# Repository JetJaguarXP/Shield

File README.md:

# USB / DC / Solar Charger, Fuel gauge, Buck-Boost Shield
# Released under the Creative Commons Attribution-ShareAlike 4.0 International License.

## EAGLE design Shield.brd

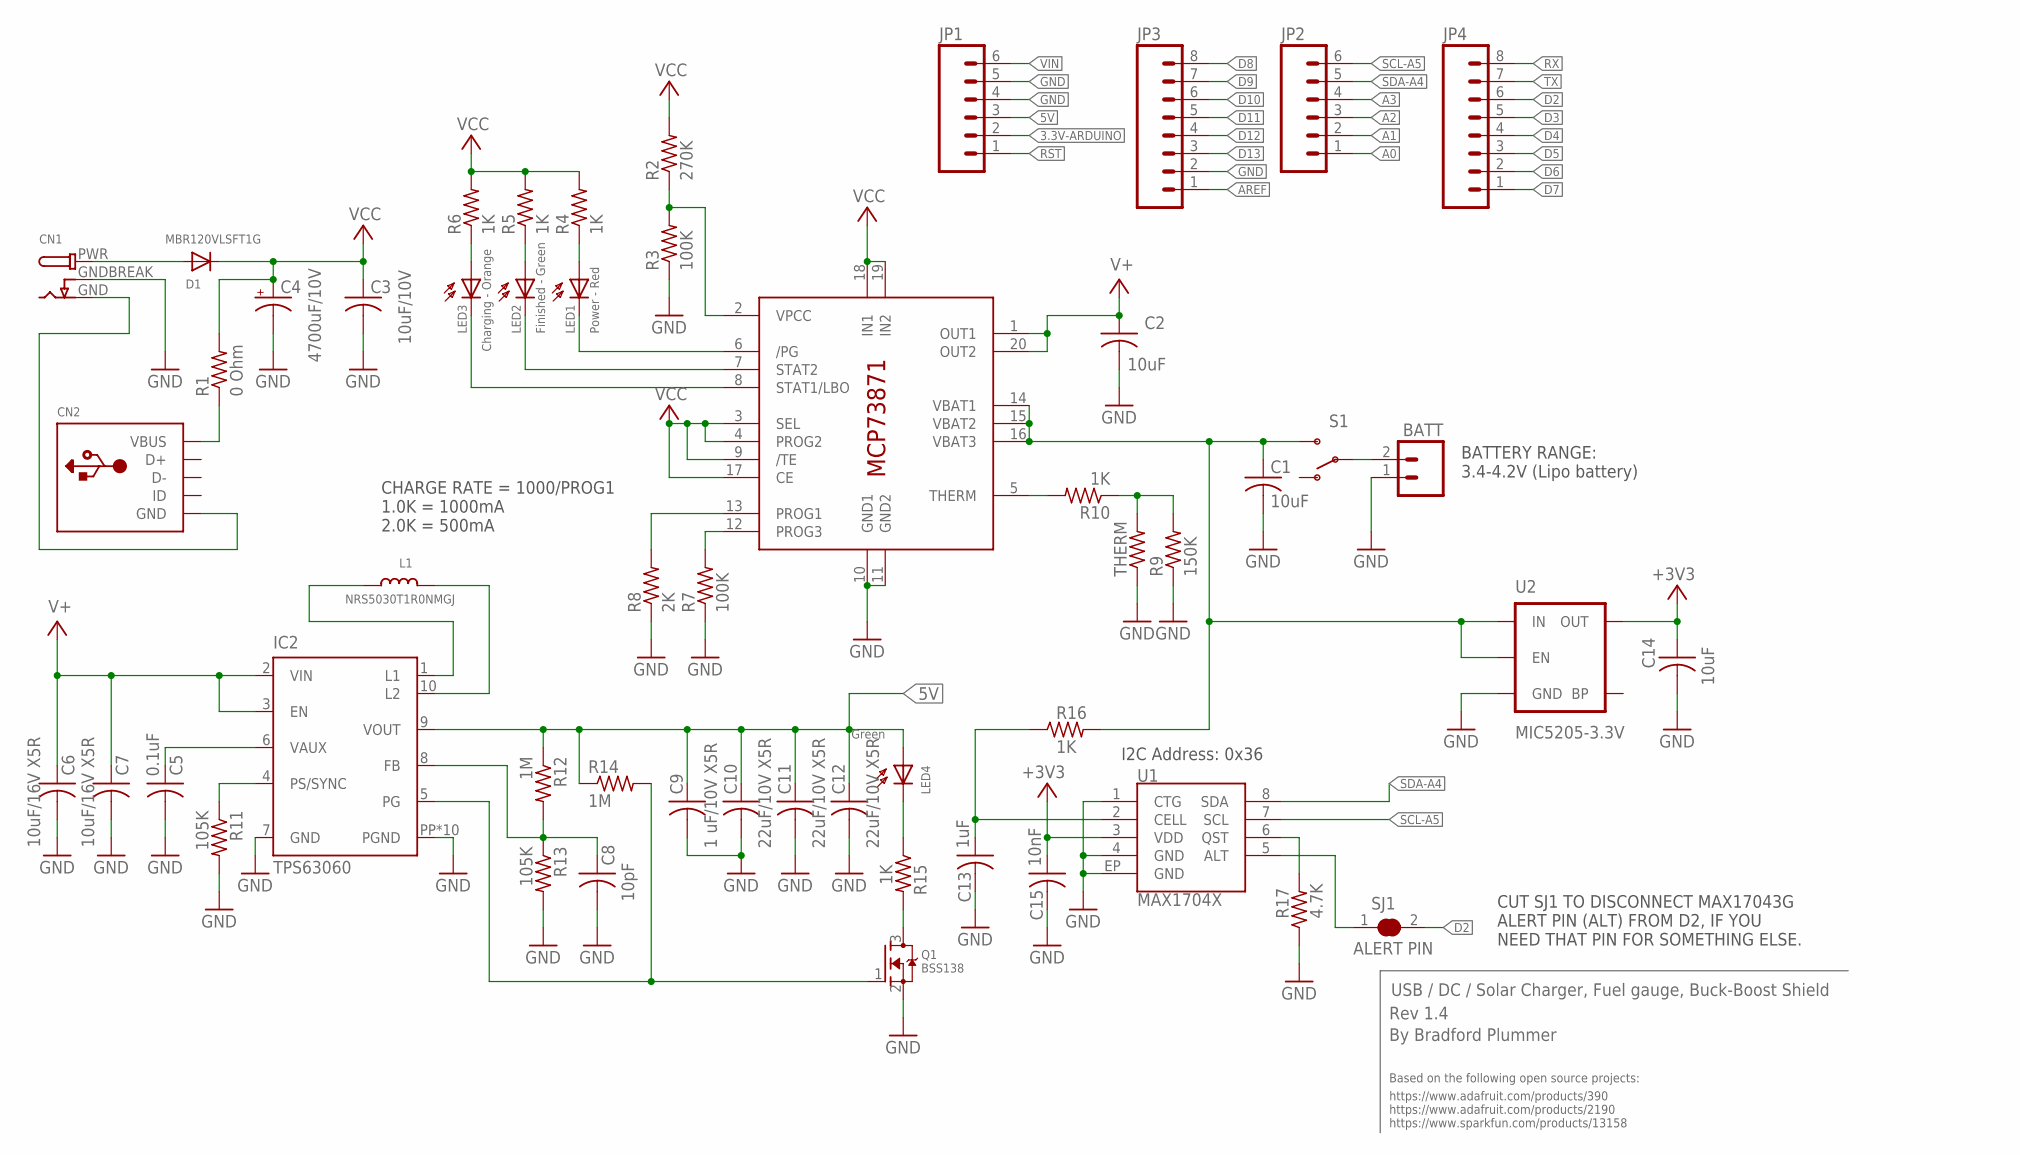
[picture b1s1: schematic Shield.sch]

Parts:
BATT: M02JST-PTH-VERT; JST-2-PTH-VERT
C1, C2, C14: 10uF; C0805K
C3: 10uF/10V; C0805K
C4: 4700uF/10V; E5-13
C5: 0.1uF; C0805K
C6, C7: 10uF/16V X5R; C0805K
C8: 10pF; C0805K
C9: 1 uF/10V X5R; C0805K
C10, C11, C12: 22uF/10V X5R; C0805K
C13: 1uF; C0805K
C15: 10nF; C0805K
CN1: DCBARREL1.3MM; DCJACK_1.3MM_PTH
CN2: USBMINIB; USB-MINIB
D1: MBR120VLSFT1G; SOD-123
IC1: MCP73871; QFN20
IC2: TPS63060; DSC-S-PWSON-N10
JP1, JP2: M06NO_SILK_FEMALE_PTH; 1X06_NO_SILK
JP3, JP4: M08NO_SILK_FEMALE_PTH; 1X08_NO_SILK
L1: NRS5030T1R0NMGJ; INDUCTOR_5X5MM_TDK_VLC5045
LED1: Power - Red; SFH205
LED2: Finished - Green; SFH205
LED3: Charging - Orange; SFH205
LED4: Green; SFH205
Q1: BSS138; SOT23-WIDE
R1: 0 Ohm; R0805
R2: 270K; R0805
R3, R7: 100K; R0805
R4, R5, R6: 1K; R0805
R8: 2K; R0805
R9: 150K; M0805
R10, R15, R16: 1K; M0805
R11, R13: 105K; M0805
R12, R14: 1M; M0805
R17: 4.7K; M0805
S1: SWITCH-SPDTPTH; SWITCH-SPDT
SJ1: ALERT PIN; SJ
THERM: R-US_FLIPFLOP; 0805-THM
U1: MAX1704X; TDFN-8
U2: MIC5205-3.3V; SOT23-5

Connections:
3.3V-ARDUINO: JP1.2
5V: C9.1, C10.1, C11.1, C12.1, IC2.9 (VOUT), JP1.3, LED4.A, R12.1, R14.1
+3V3: C14.1, C15.1, U1.3 (VDD), U2.5 (OUT)
A0: JP2.1
A1: JP2.2
A2: JP2.3
A3: JP2.4
AREF: JP3.1
D2: JP4.6, SJ1.2
D3: JP4.5
D4: JP4.4
D5: JP4.3
D6: JP4.2
D7: JP4.1
D8: JP3.8
D9: JP3.7
D10: JP3.6
D11: JP3.5
D12: JP3.4
D13: JP3.3
GND: BATT.1, C1.2, C2.2, C3.2, C4.-, C5.2, C6.2, C7.2, C8.2, C9.2, C10.2, C11.2, C12.2, C13.2, C14.2, C15.2, CN1.GNDBREAK, IC1.10 (GND1), IC1.11 (GND2), IC2.7 (GND), IC2.PP (PGND), IC2.PP@1 (PGND), IC2.PP@2 (PGND), IC2.PP@3 (PGND), IC2.PP@4 (PGND), IC2.PP@5 (PGND), IC2.PP@7 (PGND), IC2.PP@8 (PGND), IC2.PP@9 (PGND), IC2.PP@10 (PGND), JP1.4, JP1.5, JP3.2, Q1.2 (S), R3.1, R7.1, R8.1, R9.1, R11.2, R13.2, R17.1, THERM.1, U1.1 (CTG), U1.4 (GND), U1.EP (GND), U2.2 (GND)
unnamed: BATT.2, S1.2
unnamed: C1.1, IC1.14 (VBAT1), IC1.15 (VBAT2), IC1.16 (VBAT3), R16.2, S1.3 (S), U2.1 (IN), U2.3 (EN)
unnamed: CN1.PWR, D1.A
unnamed: CN1.GND, CN2.GND
unnamed: CN2.VBUS, R1.1
unnamed: IC1.2 (VPCC), R2.1, R3.2
unnamed: IC1.6 (/PG), LED1.K (C)
unnamed: IC1.7 (STAT2), LED2.K (C)
unnamed: IC1.8 (STAT1/LBO), LED3.K (C)
unnamed: LED1.A, R4.1
unnamed: LED2.A, R5.1
unnamed: LED3.A, R6.1
unnamed: IC1.5 (THERM), R10.2
unnamed: IC1.12 (PROG3), R7.2
unnamed: IC1.13 (PROG1), R8.2
unnamed: R9.2, R10.1, THERM.2
unnamed: IC2.1 (L1), L1.P$1 (1)
unnamed: IC2.10 (L2), L1.P$2 (2)
unnamed: IC2.4 (PS/SYNC), R11.1
unnamed: C5.1, IC2.6 (VAUX)
unnamed: C8.1, IC2.8 (FB), R12.2, R13.1
unnamed: Q1.3 (D), R15.2
unnamed: IC2.5 (PG), Q1.1 (G), R14.2
unnamed: LED4.K (C), R15.1
unnamed: C13.1, R16.1, U1.2 (CELL)
unnamed: R17.2, U1.6 (QST)
unnamed: SJ1.1, U1.5 (ALT)
RST: JP1.1
RX: JP4.8
SCL-A5: JP2.6, U1.7 (SCL)
SDA-A4: JP2.5, U1.8 (SDA)
TX: JP4.7
V+: C2.1, C6.1, C7.1, IC1.1 (OUT1), IC1.20 (OUT2), IC2.2 (VIN), IC2.3 (EN)
VCC: C3.1, C4.+, D1.C, IC1.3 (SEL), IC1.4 (PROG2), IC1.9 (/TE), IC1.17 (CE), IC1.18 (IN1), IC1.19 (IN2), R1.2, R2.2, R4.2, R5.2, R6.2
VIN: JP1.6

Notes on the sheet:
I2C Address: 0x36
CUT SJ1 TO DISCONNECT MAX17043G ALERT PIN (ALT) FROM D2, IF YOU NEED THAT PIN FOR SOMETHING ELSE.
CHARGE RATE = 1000/PROG1 1.0K = 1000mA 2.0K = 500mA
BATTERY RANGE: 3.4-4.2V (Lipo battery)
USB / DC / Solar Charger, Fuel gauge, Buck-Boost Shield
Rev 1.4
Based on the following open source projects:
https://www.adafruit.com/products/390 https://www.adafruit.com/products/2190 https://www.sparkfun.com/products/13158
By Bradford Plummer

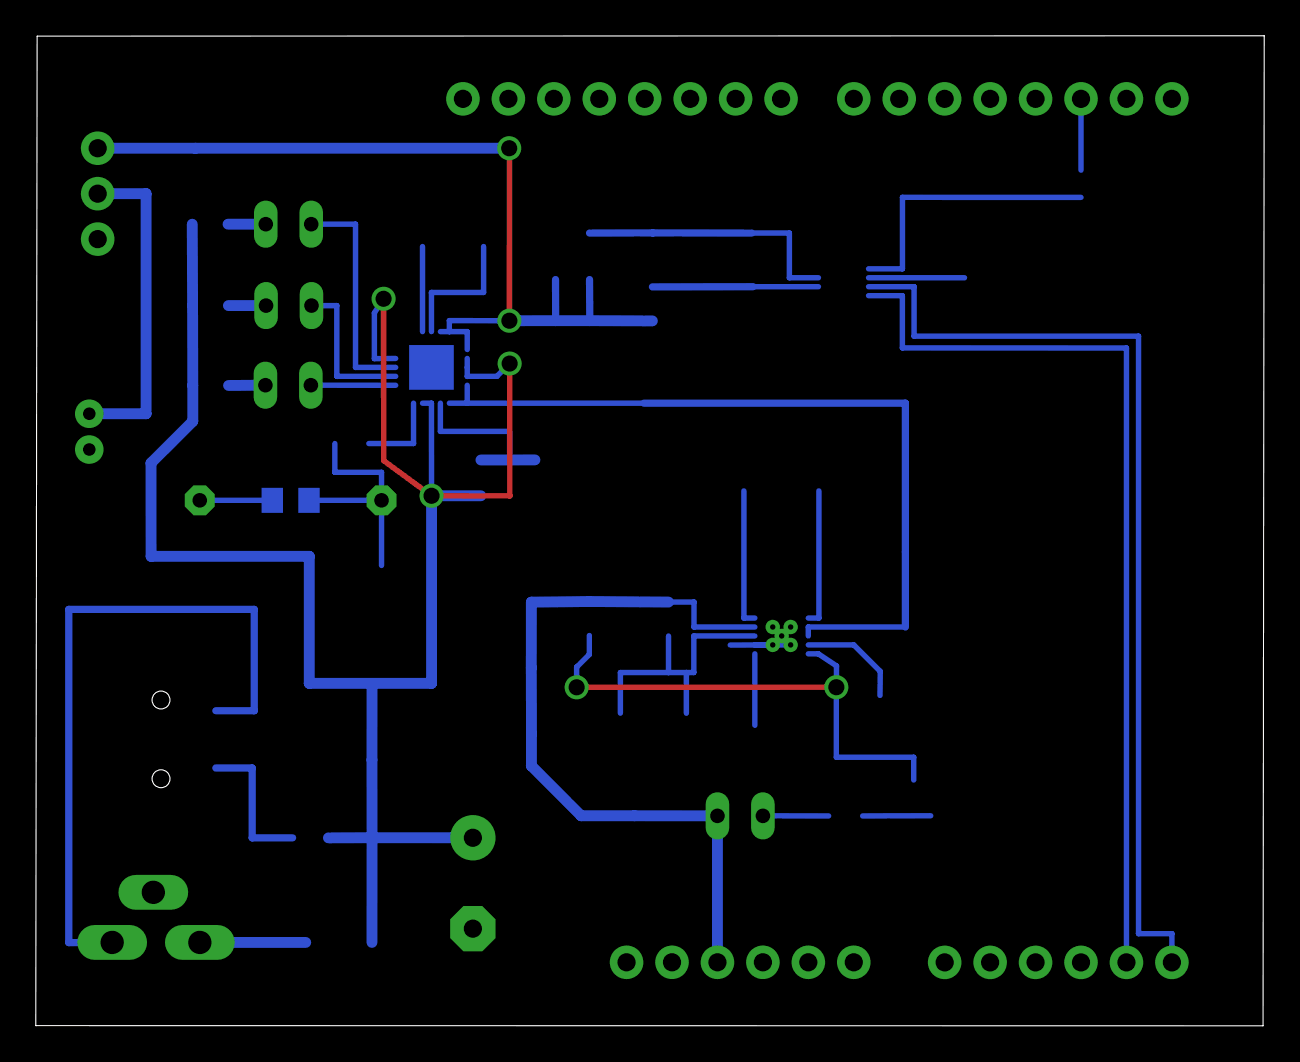
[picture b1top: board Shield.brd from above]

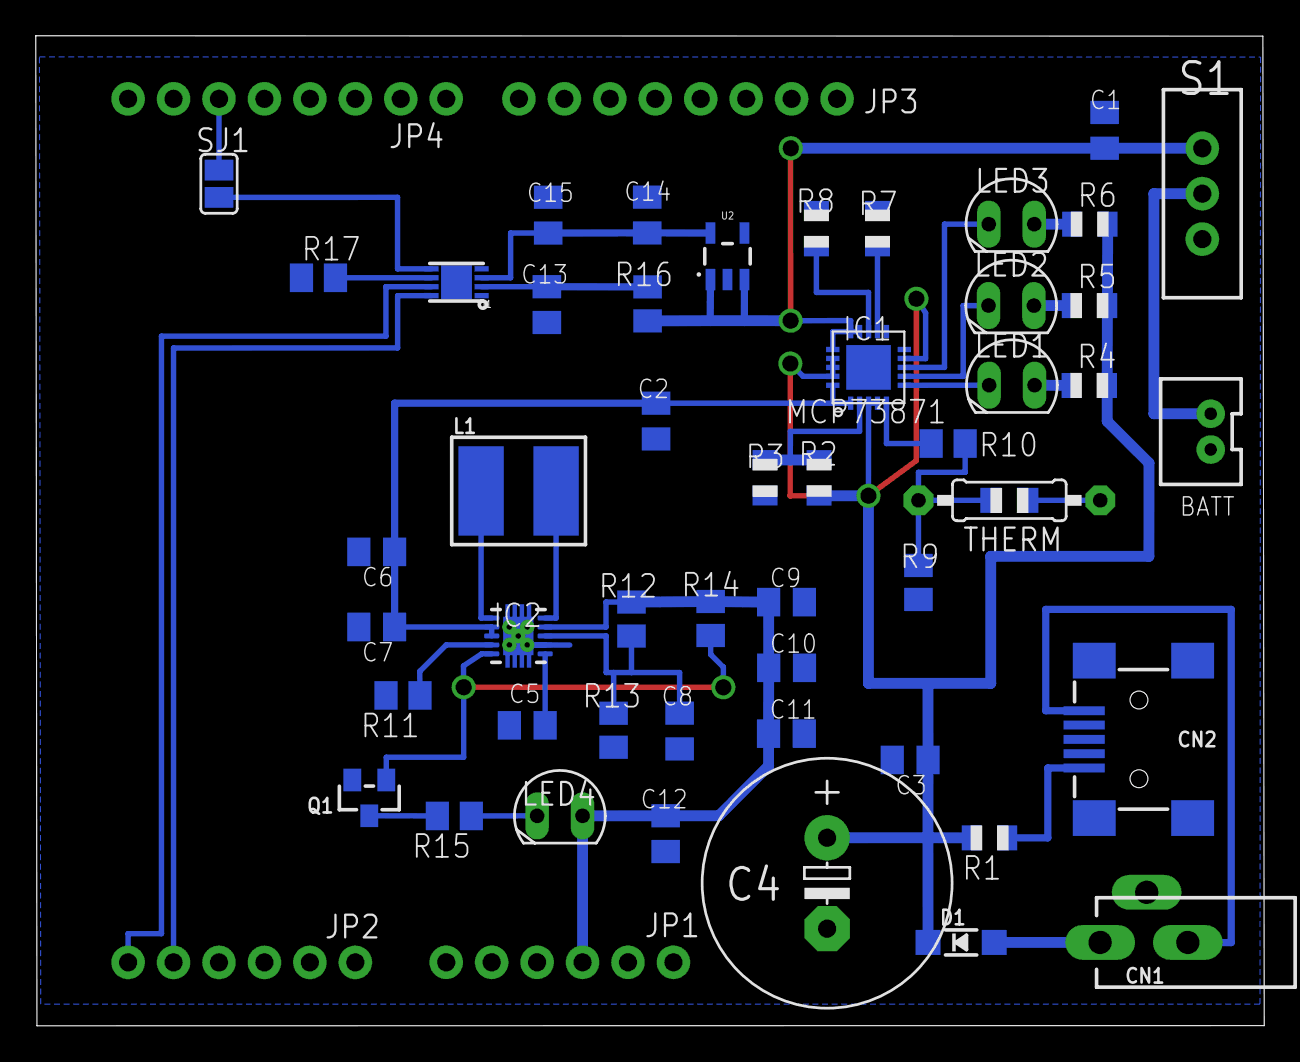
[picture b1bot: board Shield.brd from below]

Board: 2 copper layers, 68.7 x 55.3 mm, 53 parts (53 on the bottom side), 35 nets.

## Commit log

2015-11-18 Latest work on the Shield as of 17 Nov 2015
2015-11-19 Added license to the Readme file.

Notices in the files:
parts and their libraries:
SparkFun-Connectors: Licensing: Creative Commons ShareAlike 4.0 International - https://creativecommons.org/licenses/by-sa/4.0
microbuilder: This work is placed in the public domain, and may be freely used for commercial and non-commercial work with the following conditions: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
